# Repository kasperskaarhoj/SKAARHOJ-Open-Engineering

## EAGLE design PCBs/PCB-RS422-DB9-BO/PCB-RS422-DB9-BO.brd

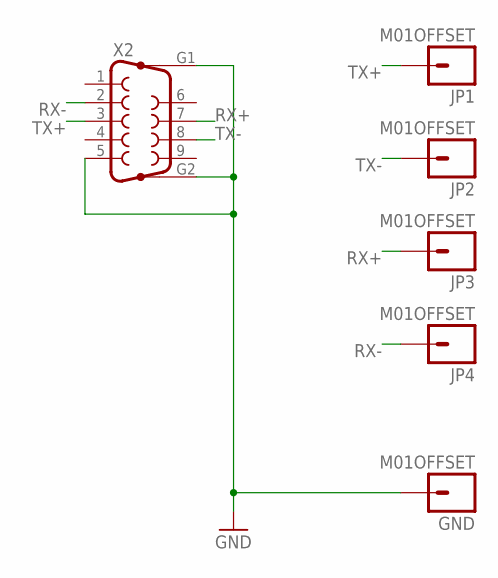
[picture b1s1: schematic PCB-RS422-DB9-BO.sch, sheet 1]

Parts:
GND: M01OFFSET; 1X01_OFFSET
JP1, JP2, JP3, JP4: M01OFFSET; 1X01_OFFSET
X2: F09HP

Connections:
GND: GND.1, X2.5, X2.G1, X2.G2
RX+: JP3.1, X2.7
RX-: JP4.1, X2.2
TX+: JP1.1, X2.3
TX-: JP2.1, X2.8

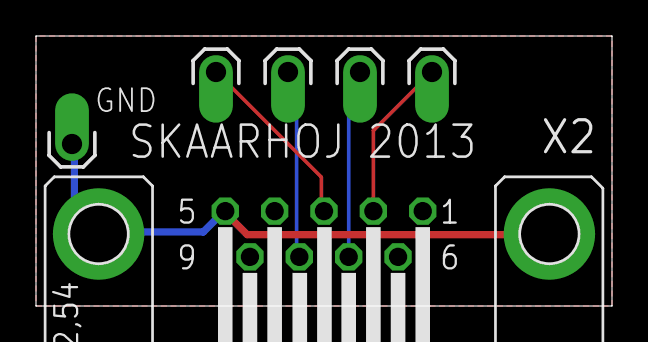
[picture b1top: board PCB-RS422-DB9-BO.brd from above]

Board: 2 copper layers, 32.0 x 15.0 mm, 6 parts (0 on the bottom side), 5 nets.

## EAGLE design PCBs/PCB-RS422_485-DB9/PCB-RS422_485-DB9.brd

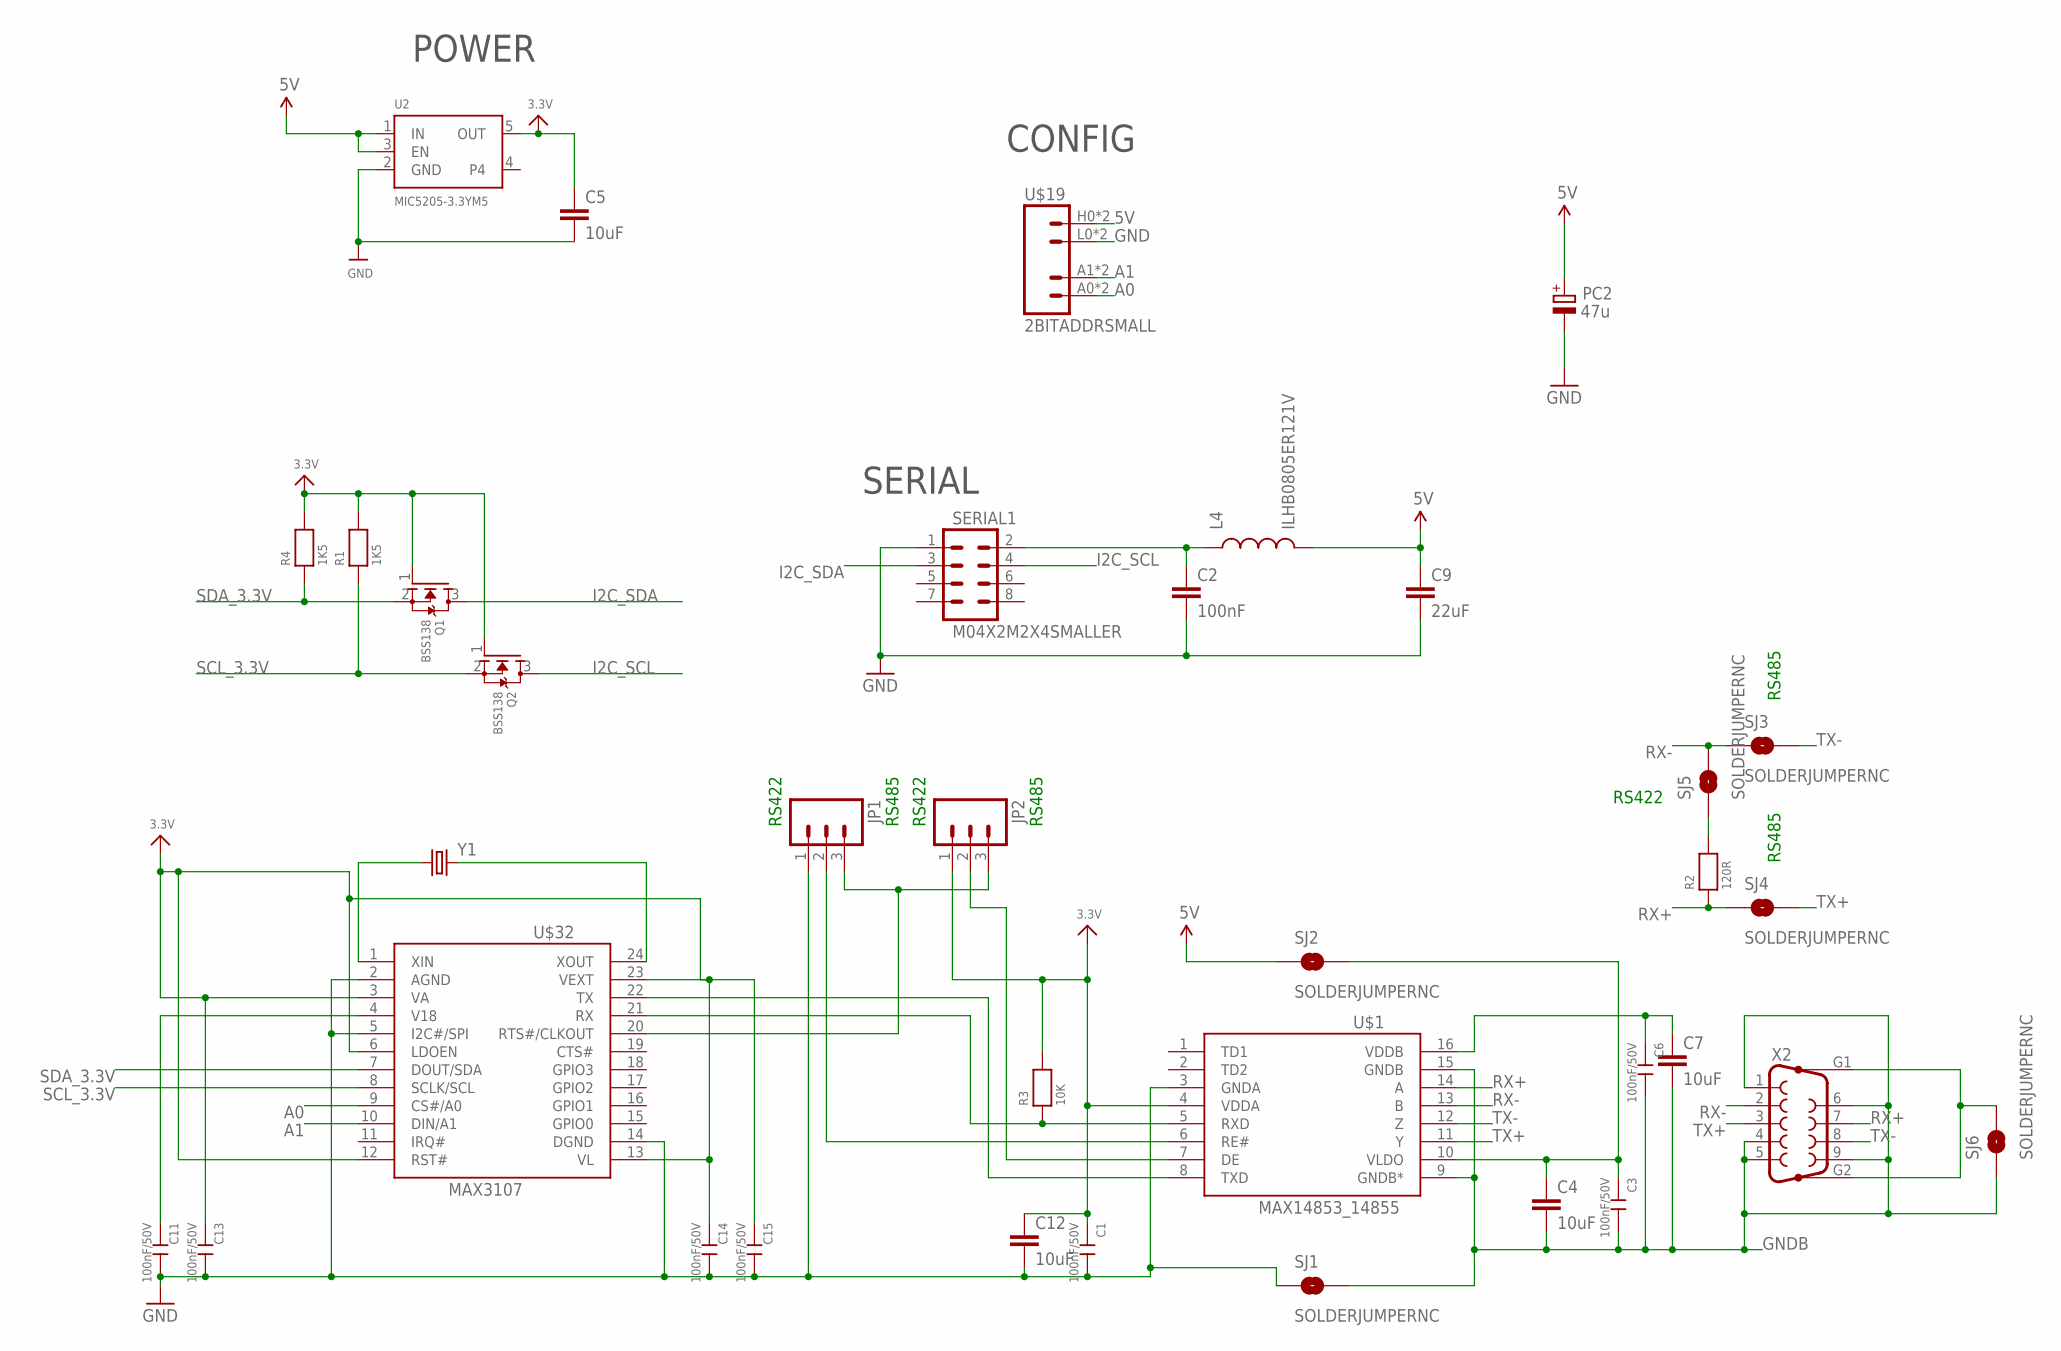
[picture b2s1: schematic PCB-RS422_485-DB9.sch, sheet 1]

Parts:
C1, C3, C6, C11, C13, C14, C15: 100nF/50V; C0603
C2: 100nF; 0603-CAP
C4, C5, C7, C12: 10uF; 0805
C9: 22uF; 0805
JP1, JP2: M03LOCK; 1X03_LOCK
L4: ILHB0805ER121V; 0805
PC2: 47u; PANASONIC_D
Q1, Q2: BSS138; SOT23-R
R1, R4: 1K5; 0603
R2: 120R; 0603
R3: 10K; 0603
SERIAL1: M04X2M2X4SMALLER; M2X4SMALLER
SJ1, SJ2, SJ3, SJ4, SJ5, SJ6: SOLDERJUMPERNC; SJ_2S
U2: MIC5205-3.3YM5; SOT23-5
U$1: MAX14853_14855; SO-16W
U$19: 2BITADDRSMALL; 2BITADDR_SMALL
U$32: MAX3107; SSOP24
X2: F09HP
Y1: CRYSTALHC49US; HC49US

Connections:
3.3V: C1.1, C5.1, C12.1, C13.1, C14.1, C15.1, JP2.1, Q1.1 (G), Q2.1 (G), R1.2, R3.2, R4.2, U2.5 (OUT), U$1.4 (VDDA), U$32.3 (VA), U$32.6 (LDOEN), U$32.12 (RST#), U$32.13 (VL), U$32.23 (VEXT)
5V: C9.1, L4.2, PC2.+, SJ2.1, U2.1 (IN), U2.3 (EN), U$19.H0 (VCC), U$19.H1 (VCC)
A0: U$19.A0 (A1), U$19.AS0 (A1), U$32.9 (CS#/A0)
A1: U$19.A1 (A2), U$19.AS1 (A2), U$32.10 (DIN/A1)
GND: C1.2, C2.2, C5.2, C9.2, C11.2, C12.2, C13.2, C14.2, C15.2, JP1.1, PC2.-, SERIAL1.1, SJ1.1, U2.2 (GND), U$1.3 (GNDA), U$19.L0 (GND), U$19.L1 (GND), U$32.2 (AGND), U$32.5 (I2C#/SPI), U$32.14 (DGND)
GNDB: C3.2, C4.2, C6.2, C7.2, SJ1.2, SJ6.1, U$1.9 (GNDB*), U$1.15 (GNDB), X2.1, X2.4, X2.5, X2.6, X2.9
I2C_SCL: Q2.3 (D), SERIAL1.4
I2C_SDA: Q1.3 (D), SERIAL1.3
unnamed: U$1.8 (TXD), U$32.22 (TX)
unnamed: R3.1, U$1.5 (RXD), U$32.21 (RX)
unnamed: C2.1, L4.1, SERIAL1.2
unnamed: R2.2, SJ5.1
unnamed: C3.1, C4.1, SJ2.2, U$1.10 (VLDO)
unnamed: C11.1, U$32.4 (V18)
unnamed: JP2.2, U$1.7 (DE)
unnamed: JP1.2, U$1.6 (RE#)
unnamed: SJ6.2, X2.G1, X2.G2
unnamed: JP1.3, JP2.3, U$32.20 (RTS#/CLKOUT)
unnamed: U$32.1 (XIN), Y1.1
unnamed: C6.1, C7.1, U$1.16 (VDDB)
unnamed: U$32.24 (XOUT), Y1.2
RX+: R2.1, SJ4.1, U$1.14 (A), X2.7
RX-: SJ3.1, SJ5.2, U$1.13 (B), X2.2
SCL_3.3V: Q2.2 (S), R1.1, U$32.8 (SCLK/SCL)
SDA_3.3V: Q1.2 (S), R4.1, U$32.7 (DOUT/SDA)
TX+: SJ4.2, U$1.11 (Y), X2.3
TX-: SJ3.2, U$1.12 (Z), X2.8

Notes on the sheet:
SERIAL
RS422
RS485
POWER
CONFIG

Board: 2 copper layers, 36 parts (0 on the bottom side), 27 nets, no tracks yet.

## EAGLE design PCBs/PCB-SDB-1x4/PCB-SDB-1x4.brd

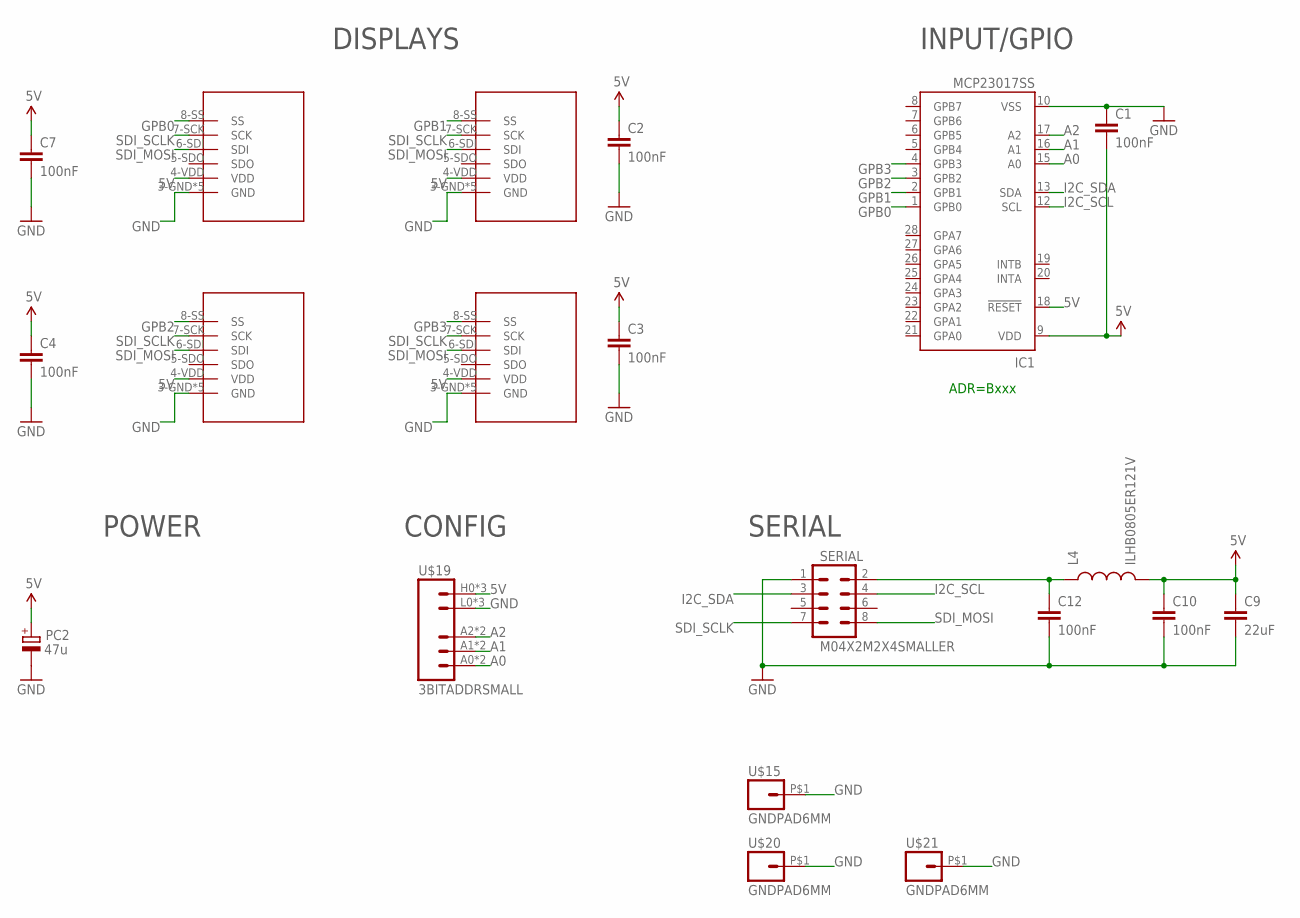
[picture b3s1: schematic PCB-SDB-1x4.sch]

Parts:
C1, C2, C3, C4, C7, C10, C12: 100nF; 0603-CAP
C9: 22uF; 0805
IC1: MCP23017SS; SSOP28; MPN MCP23017-E/SS
L4: ILHB0805ER121V; 0805
PC2: 47u; PANASONIC_D
SERIAL: M04X2M2X4SMALLER; M2X4SMALLER
SSW1, SSW2, SSW3, SSW4: SMART_DISPLAY
U$15, U$20, U$21: GNDPAD6MM; 3.2MMPAD6MM
U$19: 3BITADDRSMALL; 3BITADDR_SMALL

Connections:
5V: C1.2, C2.1, C3.1, C4.1, C7.1, C9.1, C10.1, IC1.9 (VDD), IC1.18 (!RESET), L4.2, PC2.+, SSW1.4-VDD (VDD), SSW2.4-VDD (VDD), SSW3.4-VDD (VDD), SSW4.4-VDD (VDD), U$19.H0 (VCC), U$19.H1 (VCC), U$19.H2 (VCC)
A0: IC1.15 (A0), U$19.A0, U$19.AS0 (A0)
A1: IC1.16 (A1), U$19.A1, U$19.AS1 (A1)
A2: IC1.17 (A2), U$19.A2, U$19.AS2 (A2)
ARD_5V: C12.1, L4.1, SERIAL.2
GND: C1.1, C2.2, C3.2, C4.2, C7.2, C9.2, C10.2, C12.2, IC1.10 (VSS), PC2.-, SERIAL.1, SSW1.3-GND (GND), SSW1.P$1 (GND), SSW1.P$2 (GND), SSW1.P$3 (GND), SSW1.P$4 (GND), SSW2.3-GND (GND), SSW2.P$1 (GND), SSW2.P$2 (GND), SSW2.P$3 (GND), SSW2.P$4 (GND), SSW3.3-GND (GND), SSW3.P$1 (GND), SSW3.P$2 (GND), SSW3.P$3 (GND), SSW3.P$4 (GND), SSW4.3-GND (GND), SSW4.P$1 (GND), SSW4.P$2 (GND), SSW4.P$3 (GND), SSW4.P$4 (GND), U$15.P$1, U$19.L0 (GND), U$19.L1 (GND), U$19.L2 (GND), U$20.P$1, U$21.P$1
GPB0: IC1.1 (GPB0), SSW1.8-SS (SS)
GPB1: IC1.2 (GPB1), SSW2.8-SS (SS)
GPB2: IC1.3 (GPB2), SSW3.8-SS (SS)
GPB3: IC1.4 (GPB3), SSW4.8-SS (SS)
I2C_SCL: IC1.12 (SCL), SERIAL.4
I2C_SDA: IC1.13 (SDA), SERIAL.3
SDI_MOSI: SERIAL.8, SSW1.6-SDI (SDI), SSW2.6-SDI (SDI), SSW3.6-SDI (SDI), SSW4.6-SDI (SDI)
SDI_SCLK: SERIAL.7, SSW1.7-SCK (SCK), SSW2.7-SCK (SCK), SSW3.7-SCK (SCK), SSW4.7-SCK (SCK)

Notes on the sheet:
ADR=Bxxx
INPUT/GPIO
POWER
SERIAL
DISPLAYS
CONFIG

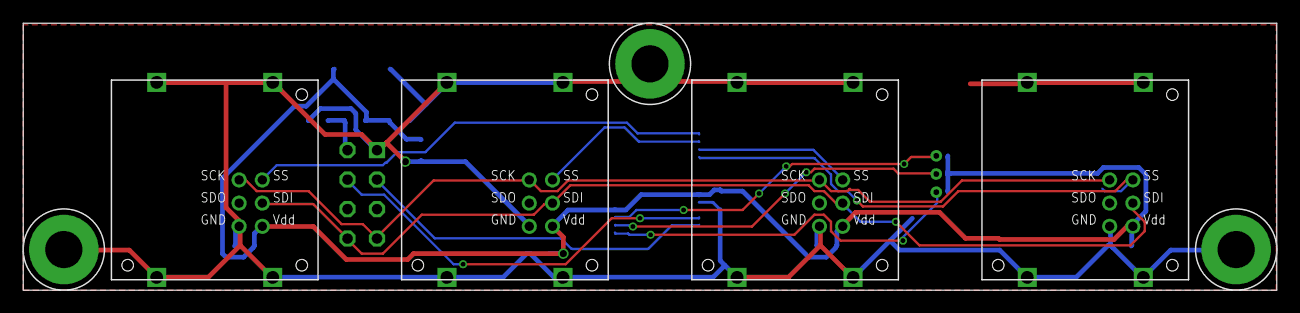
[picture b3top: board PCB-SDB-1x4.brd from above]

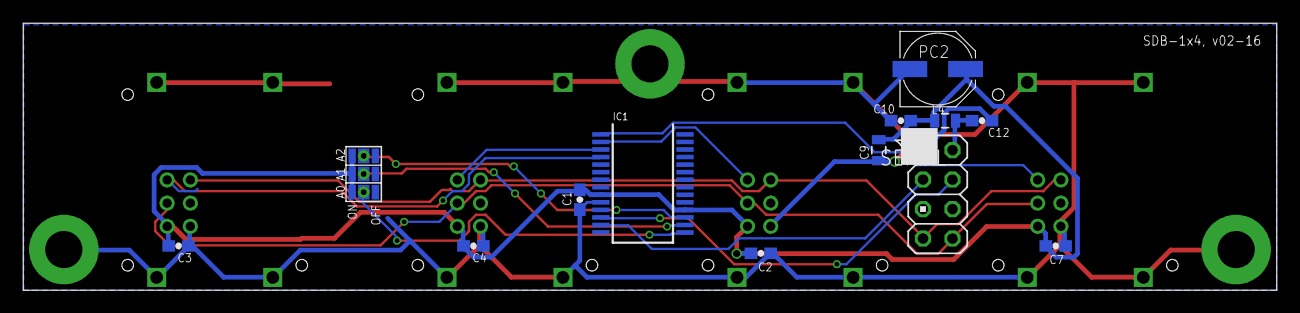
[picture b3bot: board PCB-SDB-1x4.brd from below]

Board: 2 copper layers, 108.0 x 23.0 mm, 20 parts (13 on the bottom side), 14 nets.

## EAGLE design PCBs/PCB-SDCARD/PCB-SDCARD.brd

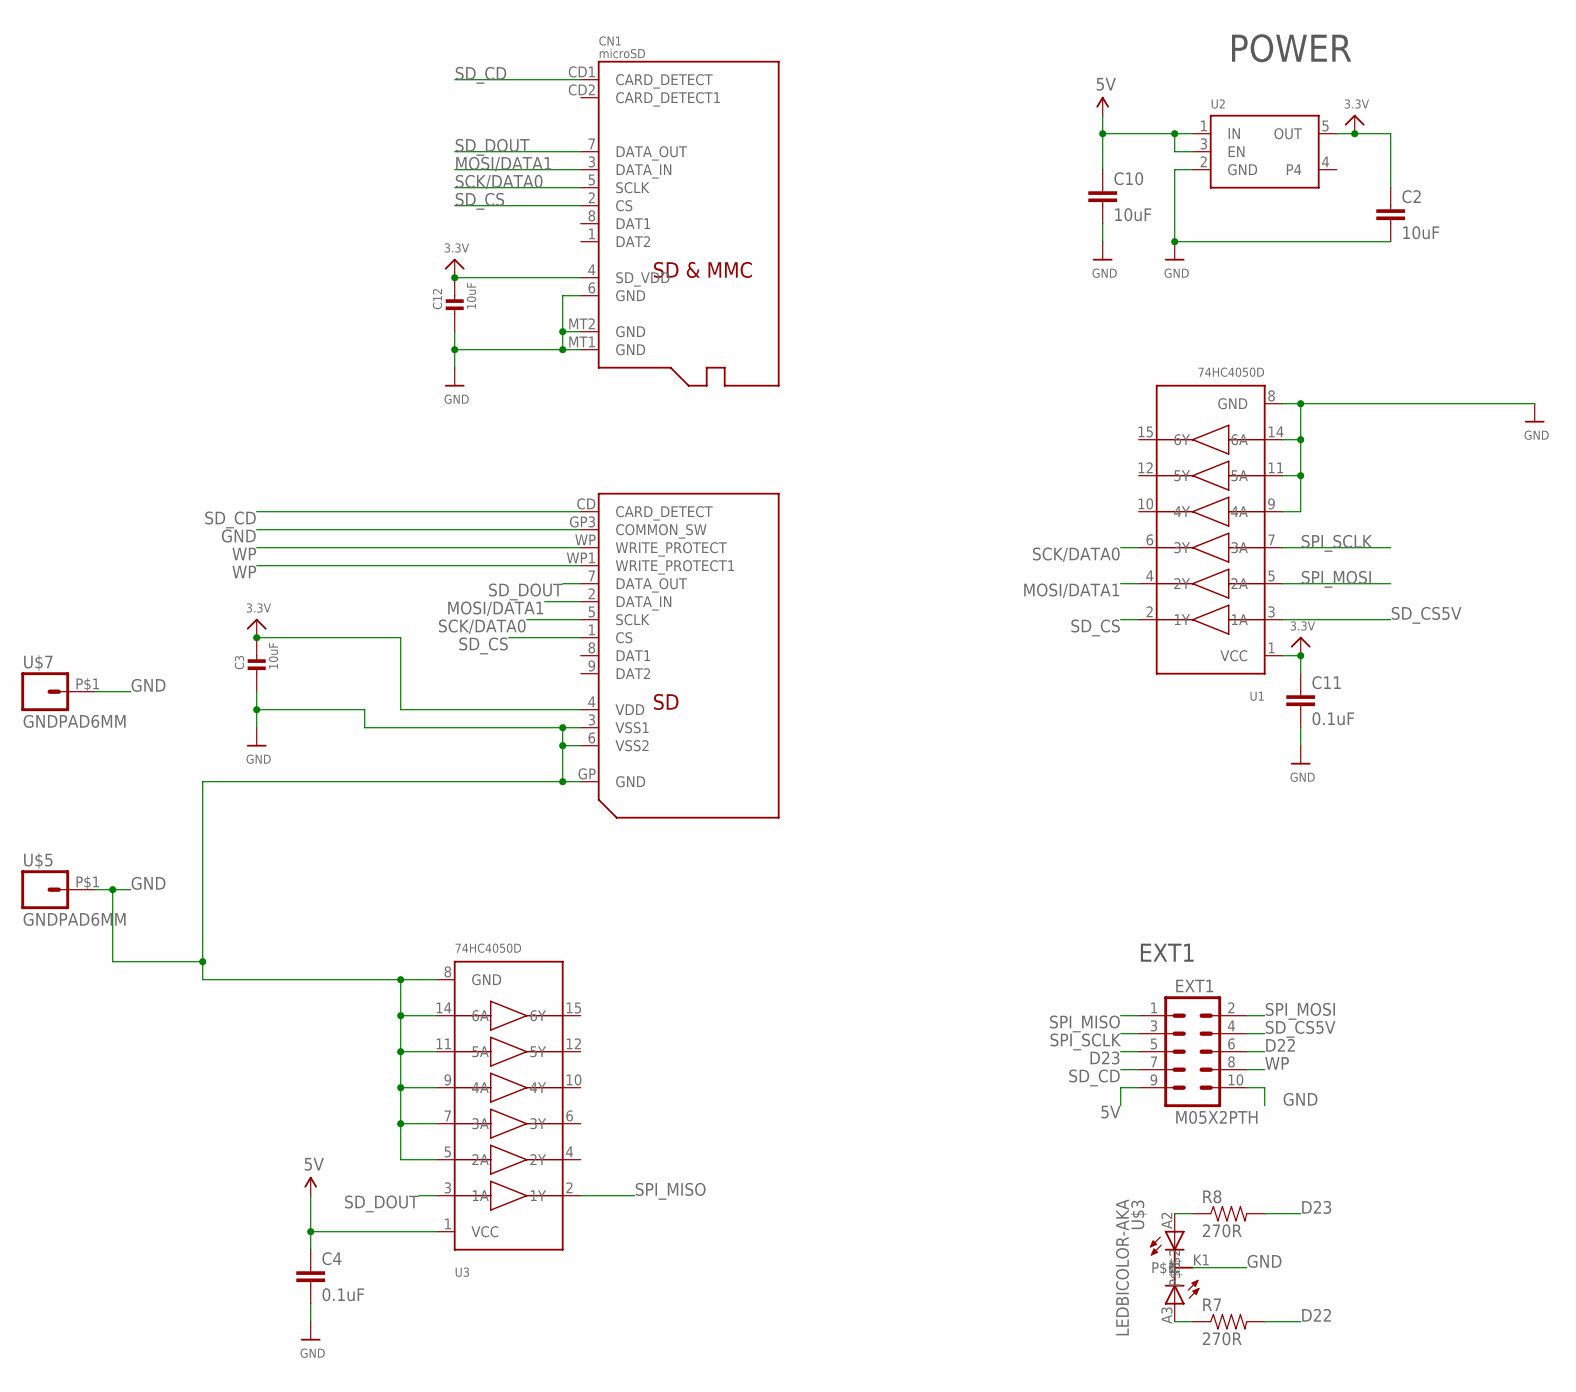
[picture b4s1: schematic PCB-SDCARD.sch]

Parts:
C2, C3, C10, C12: 10uF; 0805
C4, C11: 0.1uF; 0603-CAP
CN1: microSD; MICROSD
EXT1: M05X2PTH; AVR_ICSP
R7, R8: 270R; 0603-RES
U1, U3: 74HC4050D; TSSOP16
U2: VREG_SOT23-5; SOT23-5
U$2: SD06132; SD_LARGE
U$3: LEDBICOLOR-AKA; LED5MM-BICOLOR
U$5, U$7: GNDPAD6MM; 3.2MMPAD6MM

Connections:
3.3V: C2.1, C3.1, C11.1, C12.1, CN1.4 (SD_VDD), U1.1 (VCC), U2.5 (OUT), U$2.4 (VDD)
5V: C4.1, C10.1, EXT1.9, U2.1 (IN), U2.3 (EN), U3.1 (VCC)
D22: EXT1.6, R7.2
D23: EXT1.5, R8.2
GND: C2.2, C3.2, C4.2, C10.2, C11.2, C12.2, CN1.6 (GND), CN1.MT1 (GND), CN1.MT2 (GND), EXT1.10, U1.8 (GND), U1.9 (4A), U1.11 (5A), U1.14 (6A), U2.2 (GND), U3.5 (2A), U3.7 (3A), U3.8 (GND), U3.9 (4A), U3.11 (5A), U3.14 (6A), U$2.3 (VSS1), U$2.6 (VSS2), U$2.GP (GND), U$2.GP3 (COMMON_SW), U$3.K1, U$5.P$1, U$7.P$1
MOSI/DATA1: CN1.3 (DATA_IN), U1.4 (2Y), U$2.2 (DATA_IN)
unnamed: R8.1, U$3.A2
unnamed: R7.1, U$3.A3
SCK/DATA0: CN1.5 (SCLK), U1.6 (3Y), U$2.5 (SCLK)
SD_CD: CN1.CD1 (CARD_DETECT), EXT1.7, U$2.CD (CARD_DETECT)
SD_CS: CN1.2 (CS), U1.2 (1Y), U$2.1 (CS)
SD_CS5V: EXT1.4, U1.3 (1A)
SD_DOUT: CN1.7 (DATA_OUT), U3.3 (1A), U$2.7 (DATA_OUT)
SPI_MISO: EXT1.1, U3.2 (1Y)
SPI_MOSI: EXT1.2, U1.5 (2A)
SPI_SCLK: EXT1.3, U1.7 (3A)
WP: EXT1.8, U$2.WP (WRITE_PROTECT), U$2.WP1 (WRITE_PROTECT1)

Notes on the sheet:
POWER
EXT1

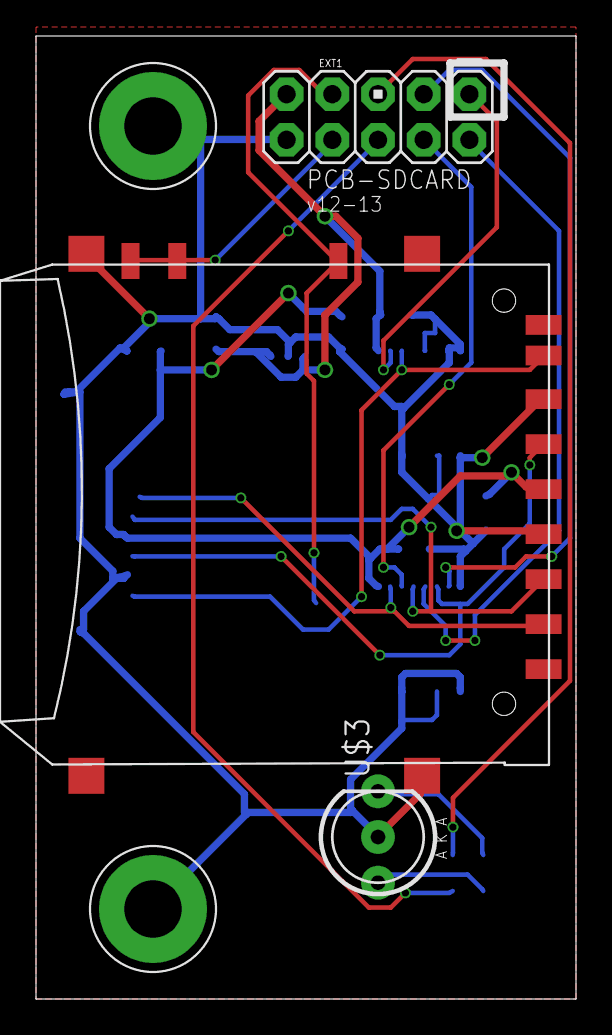
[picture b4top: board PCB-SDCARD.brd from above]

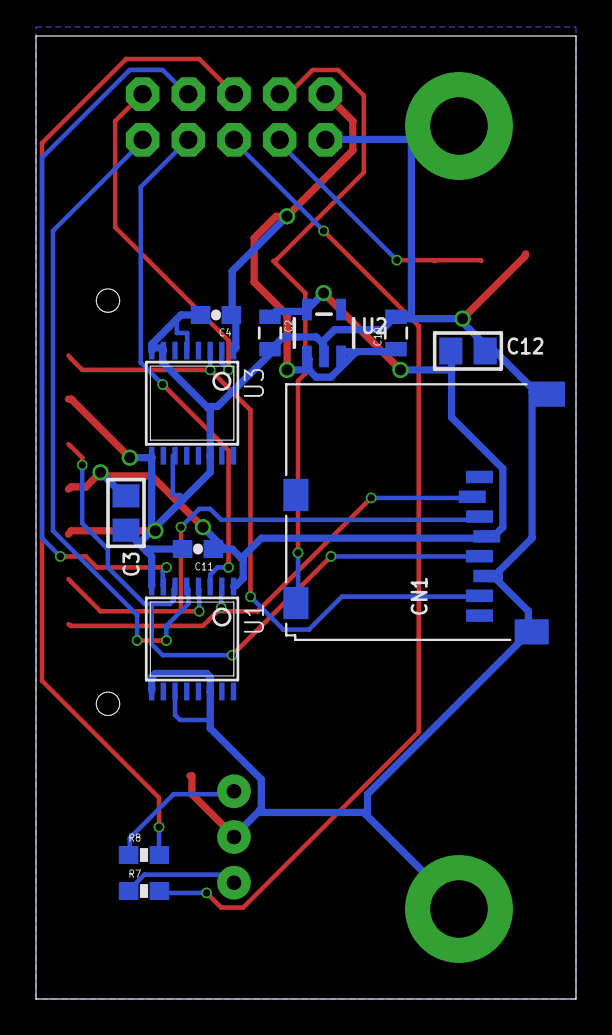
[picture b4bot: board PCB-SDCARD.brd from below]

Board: 4 copper layers, 30.0 x 53.5 mm, 17 parts (12 on the bottom side), 17 nets.

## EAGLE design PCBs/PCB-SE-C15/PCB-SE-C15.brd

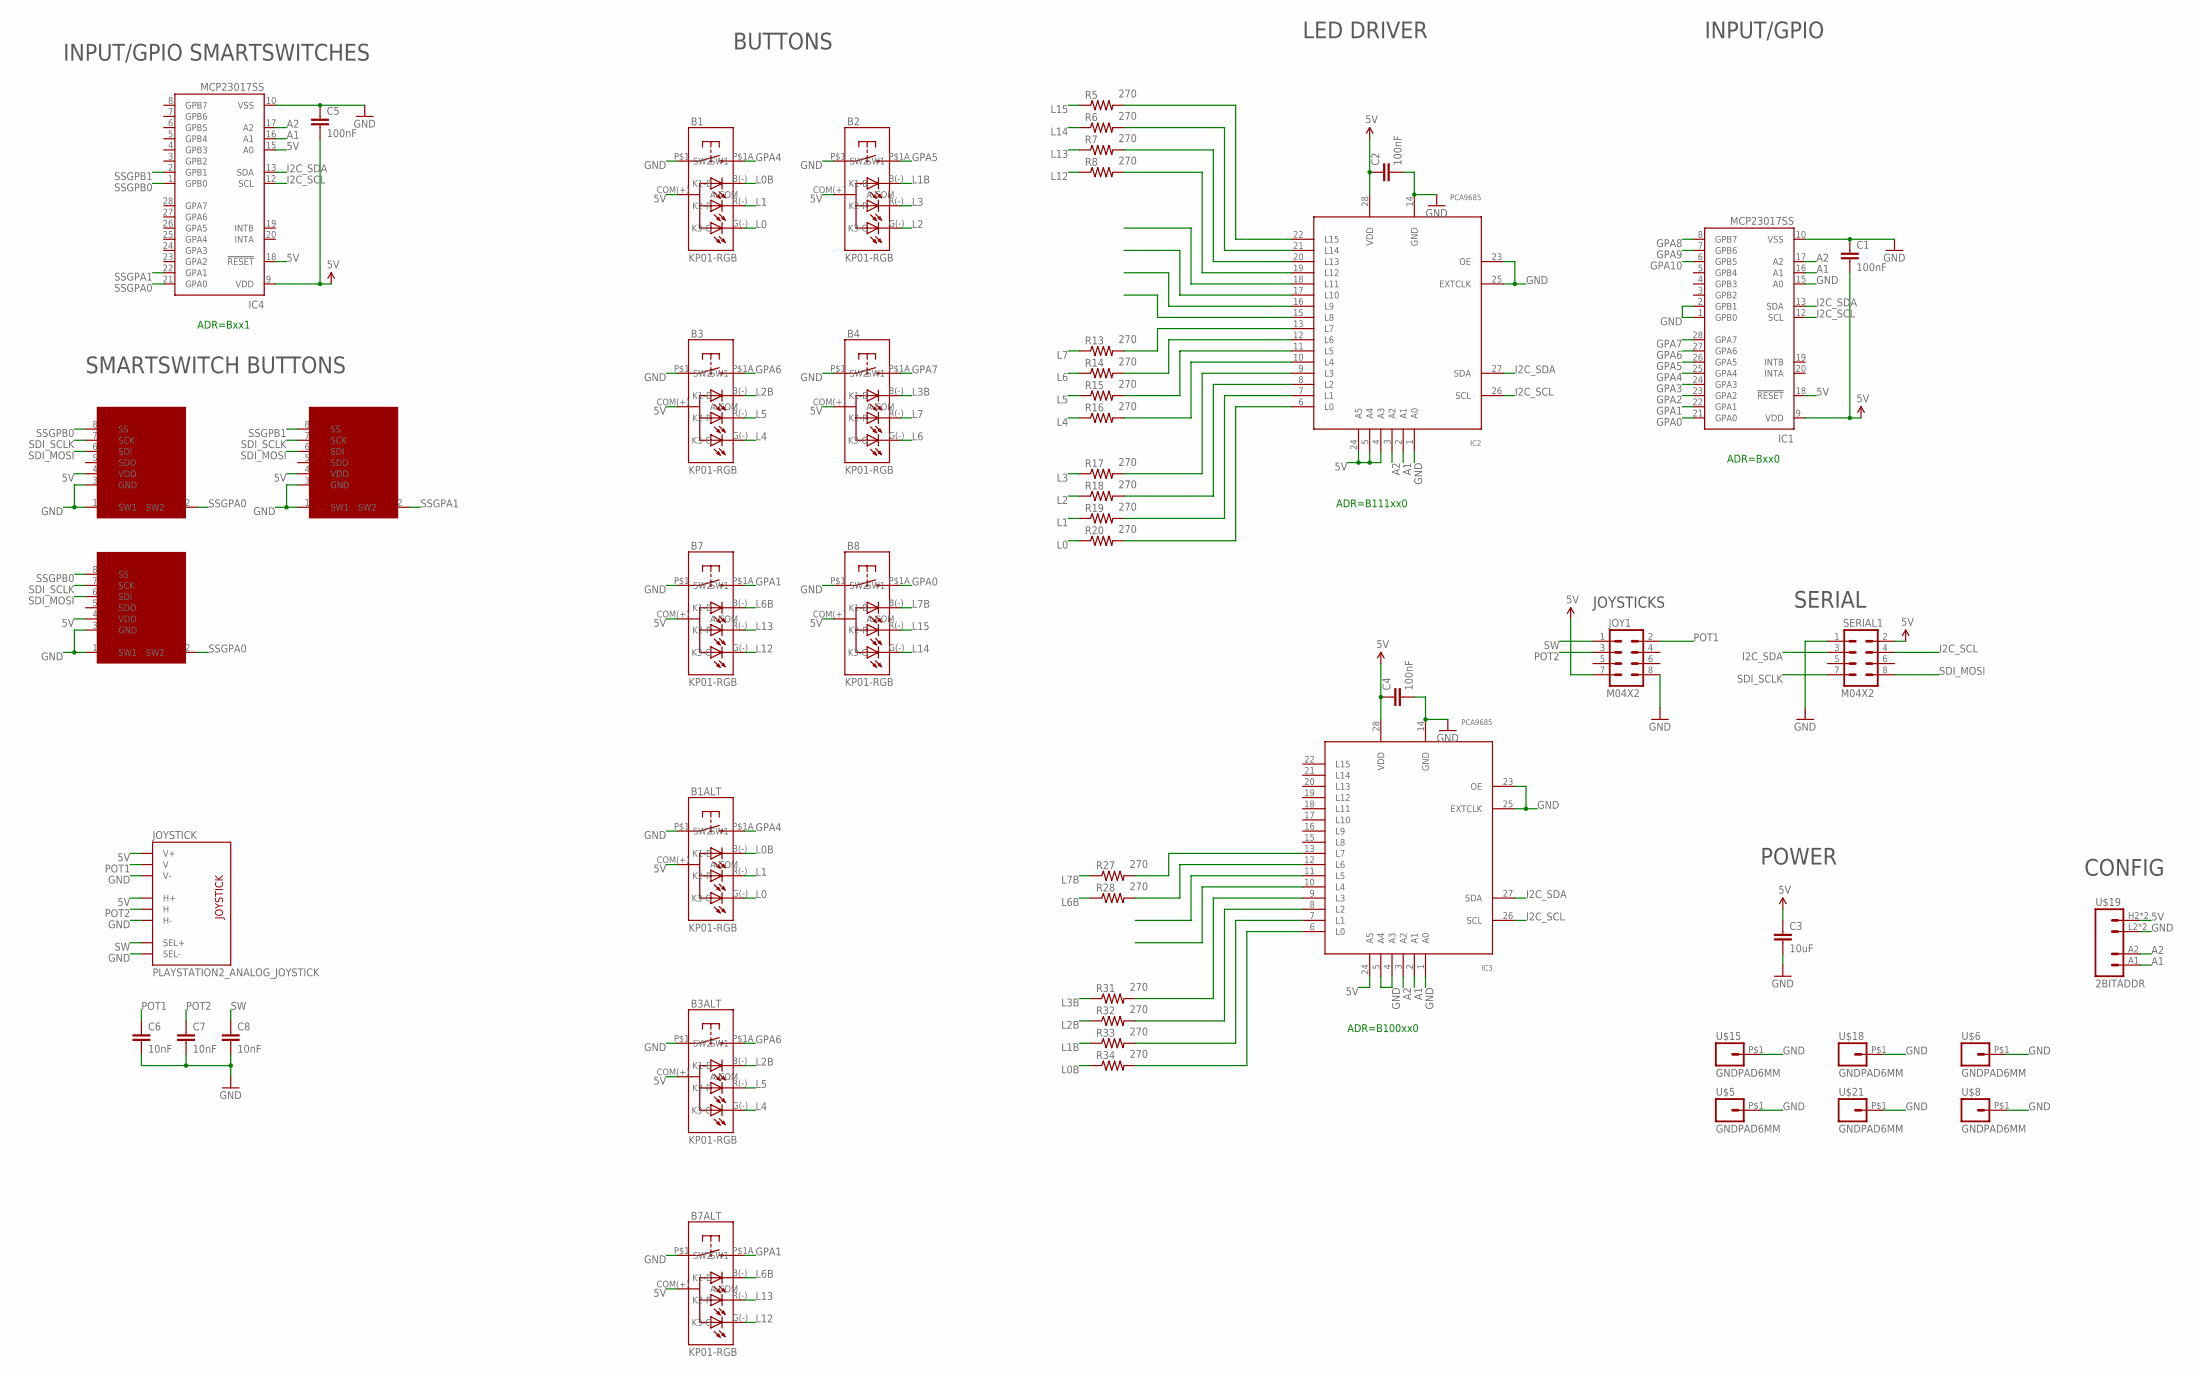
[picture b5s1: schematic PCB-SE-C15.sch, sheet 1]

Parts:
B1, B1ALT, B2, B3, B3ALT, B4, B7, B7ALT, B8: KP01-RGB; NKK-KP01
C1, C2, C4, C5: 100nF; 0603-CAP
C3: 10uF; 0805
C6, C7, C8: 10nF; 0603-CAP
IC1, IC4: MCP23017SS; SSOP28; MPN MCP23017-E/SS
IC2, IC3: PCA9685; TSSOP28
JOY1: M04X2; 2X4
JOYSTICK: PLAYSTATION2_ANALOG_JOYSTICK
R5, R6, R7, R8, R13, R14, R15, R16, R17, R18, R19, R20, R27, R28, R31, R32, R33, R34: 270; 0603-RES
SERIAL1: M04X2; 2X4
SSW1, SSW1ALT, SSW2: SMART_SWITCHSMART_SWITCH_8PIN; SMART_SWITCH
U$5, U$6, U$8, U$15, U$18, U$21: GNDPAD6MM; 3.2MMPAD6MM
U$19: 2BITADDR

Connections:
5V: B1.COM(+) (A-COM), B1ALT.COM(+) (A-COM), B2.COM(+) (A-COM), B3.COM(+) (A-COM), B3ALT.COM(+) (A-COM), B4.COM(+) (A-COM), B7.COM(+) (A-COM), B7ALT.COM(+) (A-COM), B8.COM(+) (A-COM), C1.2, C2.1, C3.1, C4.1, C5.2, IC1.9 (VDD), IC1.18 (!RESET), IC2.4 (A3), IC2.5 (A4), IC2.24 (A5), IC2.28 (VDD), IC3.24 (A5), IC3.28 (VDD), IC4.9 (VDD), IC4.15 (A0), IC4.18 (!RESET), JOY1.7, JOYSTICK.H1 (H+), JOYSTICK.V1 (V+), SERIAL1.2, SSW1.4 (VDD), SSW1ALT.4 (VDD), SSW2.4 (VDD), U$19.H2 (VCC), U$19.H3 (VCC)
A1: IC1.16 (A1), IC2.2 (A1), IC3.2 (A1), IC4.16 (A1), U$19.A1
A2: IC1.17 (A2), IC2.3 (A2), IC3.3 (A2), IC4.17 (A2), U$19.A2
GND: B1.P$1 (SW1), B1ALT.P$1 (SW1), B2.P$1 (SW1), B3.P$1 (SW1), B3ALT.P$1 (SW1), B4.P$1 (SW1), B7.P$1 (SW1), B7ALT.P$1 (SW1), B8.P$1 (SW1), C1.1, C2.2, C3.2, C4.2, C5.1, C6.2, C7.2, C8.2, IC1.1 (GPB0), IC1.2 (GPB1), IC1.10 (VSS), IC1.15 (A0), IC2.1 (A0), IC2.14 (GND), IC2.23 (OE), IC2.25 (EXTCLK), IC3.1 (A0), IC3.4 (A3), IC3.5 (A4), IC3.14 (GND), IC3.23 (OE), IC3.25 (EXTCLK), IC4.10 (VSS), JOY1.8, JOYSTICK.B2A (SEL-), JOYSTICK.H3 (H-), JOYSTICK.V3 (V-), SERIAL1.1, SSW1.1 (SW1), SSW1.3 (GND), SSW1ALT.1 (SW1), SSW1ALT.3 (GND), SSW2.1 (SW1), SSW2.3 (GND), U$5.P$1, U$6.P$1, U$8.P$1, U$15.P$1, U$18.P$1, U$19.L2 (GND), U$19.L3 (GND), U$21.P$1
GPA0: B8.P$1A (SW2), IC1.21 (GPA0)
GPA1: B7.P$1A (SW2), B7ALT.P$1A (SW2), IC1.22 (GPA1)
GPA2: IC1.23 (GPA2)
GPA3: IC1.24 (GPA3)
GPA4: B1.P$1A (SW2), B1ALT.P$1A (SW2), IC1.25 (GPA4)
GPA5: B2.P$1A (SW2), IC1.26 (GPA5)
GPA6: B3.P$1A (SW2), B3ALT.P$1A (SW2), IC1.27 (GPA6)
GPA7: B4.P$1A (SW2), IC1.28 (GPA7)
GPA8: IC1.8 (GPB7)
GPA9: IC1.7 (GPB6)
GPA10: IC1.6 (GPB5)
I2C_SCL: IC1.12 (SCL), IC2.26 (SCL), IC3.26 (SCL), IC4.12 (SCL), SERIAL1.4
I2C_SDA: IC1.13 (SDA), IC2.27 (SDA), IC3.27 (SDA), IC4.13 (SDA), SERIAL1.3
L0: B1.G(-) (K3-G), B1ALT.G(-) (K3-G), R20.1
L0B: B1.B(-) (K1-B), B1ALT.B(-) (K1-B), R34.1
L1: B1.R(-) (K2-R), B1ALT.R(-) (K2-R), R19.1
L1B: B2.B(-) (K1-B), R33.1
L2: B2.G(-) (K3-G), R18.1
L2B: B3.B(-) (K1-B), B3ALT.B(-) (K1-B), R32.1
L3: B2.R(-) (K2-R), R17.1
L3B: B4.B(-) (K1-B), R31.1
L4: B3.G(-) (K3-G), B3ALT.G(-) (K3-G), R16.1
L5: B3.R(-) (K2-R), B3ALT.R(-) (K2-R), R15.1
L6: B4.G(-) (K3-G), R14.1
L6B: B7.B(-) (K1-B), B7ALT.B(-) (K1-B), R28.1
L7: B4.R(-) (K2-R), R13.1
L7B: B8.B(-) (K1-B), R27.1
L12: B7.G(-) (K3-G), B7ALT.G(-) (K3-G), R8.1
L13: B7.R(-) (K2-R), B7ALT.R(-) (K2-R), R7.1
L14: B8.G(-) (K3-G), R6.1
L15: B8.R(-) (K2-R), R5.1
unnamed: IC3.13 (L7), R27.2
unnamed: IC3.12 (L6), R28.2
unnamed: IC2.13 (L7), R13.2
unnamed: IC2.12 (L6), R14.2
unnamed: IC2.11 (L5), R15.2
unnamed: IC2.10 (L4), R16.2
unnamed: IC2.9 (L3), R17.2
unnamed: IC2.8 (L2), R18.2
unnamed: IC2.7 (L1), R19.2
unnamed: IC3.9 (L3), R31.2
unnamed: IC3.8 (L2), R32.2
unnamed: IC3.7 (L1), R33.2
unnamed: IC3.6 (L0), R34.2
unnamed: IC2.6 (L0), R20.2
unnamed: IC2.19 (L12), R8.2
unnamed: IC2.20 (L13), R7.2
unnamed: IC2.21 (L14), R6.2
unnamed: IC2.22 (L15), R5.2
POT1: C6.1, JOY1.2, JOYSTICK.V2 (V)
POT2: C7.1, JOY1.3, JOYSTICK.H2 (H)
SDI_MOSI: SERIAL1.8, SSW1.6 (SDI), SSW1ALT.6 (SDI), SSW2.6 (SDI)
SDI_SCLK: SERIAL1.7, SSW1.7 (SCK), SSW1ALT.7 (SCK), SSW2.7 (SCK)
SSGPA0: IC4.21 (GPA0), SSW1.2 (SW2), SSW1ALT.2 (SW2)
SSGPA1: IC4.22 (GPA1), SSW2.2 (SW2)
SSGPB0: IC4.1 (GPB0), SSW1.8 (SS), SSW1ALT.8 (SS)
SSGPB1: IC4.2 (GPB1), SSW2.8 (SS)
SW: C8.1, JOY1.1, JOYSTICK.B1A (SEL+)

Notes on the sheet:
ADR=B111xx0
ADR=Bxx0
BUTTONS
LED DRIVER
INPUT/GPIO
POWER
ADR=B100xx0
ADR=Bxx1
INPUT/GPIO SMARTSWITCHES
SERIAL
SMARTSWITCH BUTTONS
JOYSTICKS
CONFIG

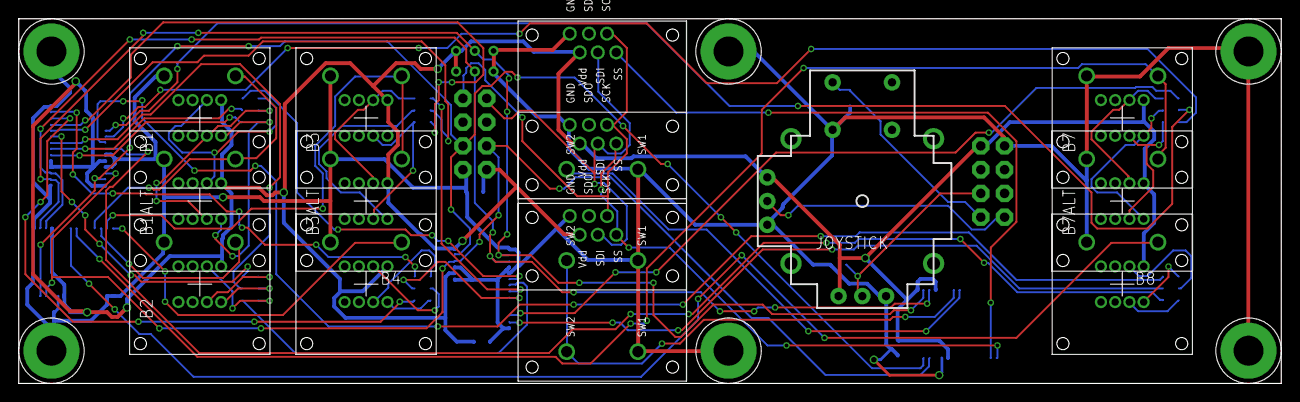
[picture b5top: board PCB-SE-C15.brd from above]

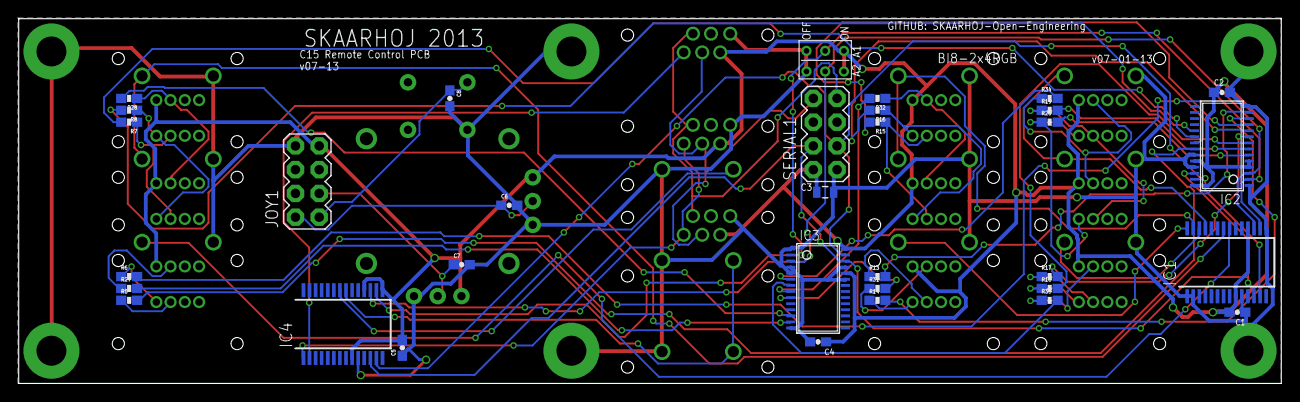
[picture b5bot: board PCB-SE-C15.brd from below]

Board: 2 copper layers, 135.0 x 39.0 mm, 52 parts (33 on the bottom side), 57 nets.

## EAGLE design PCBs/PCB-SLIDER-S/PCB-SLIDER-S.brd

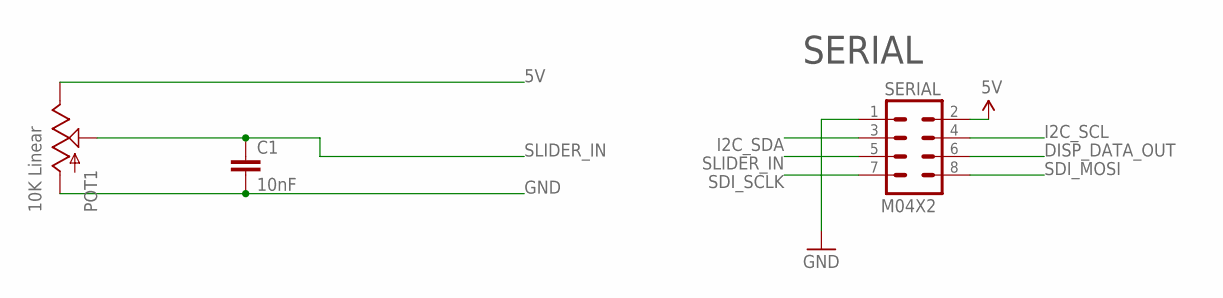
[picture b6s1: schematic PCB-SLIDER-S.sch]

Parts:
C1: 10nF; 0603-CAP
POT1: 10K Linear; SLIDER60
SERIAL: M04X2; 2X4

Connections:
5V: POT1.1 (E), SERIAL.2
DISP_DATA_OUT: SERIAL.6
GND: C1.2, POT1.3 (A), SERIAL.1
I2C_SCL: SERIAL.4
I2C_SDA: SERIAL.3
SDI_MOSI: SERIAL.8
SDI_SCLK: SERIAL.7
SLIDER_IN: C1.1, POT1.2A (S), SERIAL.5

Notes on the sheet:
SERIAL

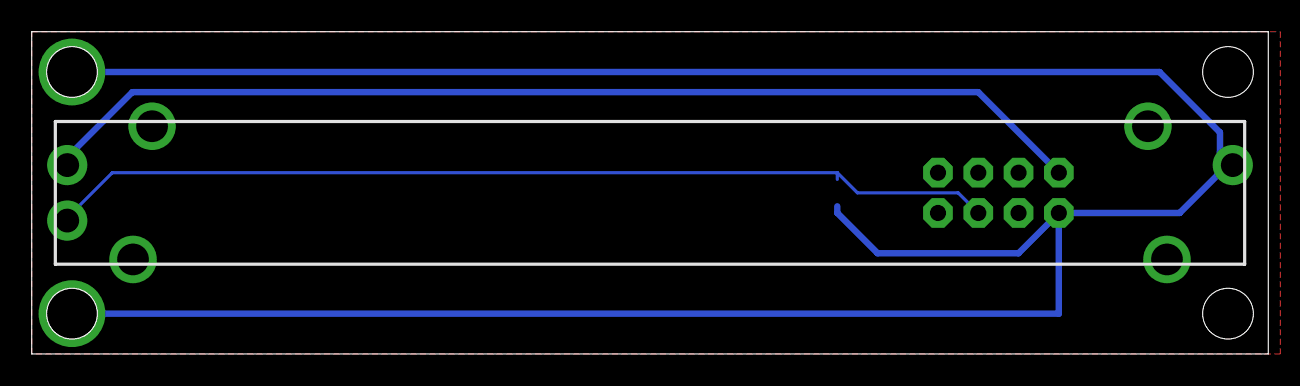
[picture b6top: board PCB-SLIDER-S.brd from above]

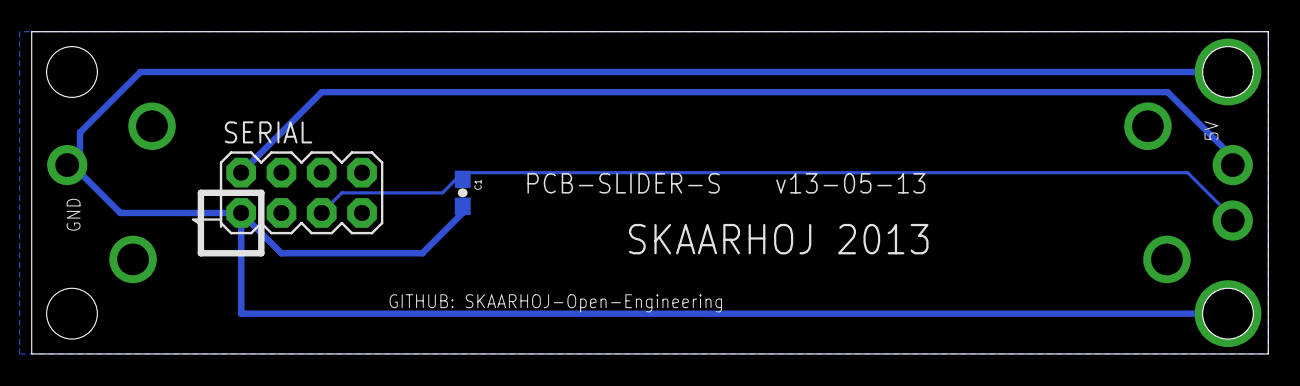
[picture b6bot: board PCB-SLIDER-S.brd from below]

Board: 2 copper layers, 78.0 x 20.3 mm, 3 parts (2 on the bottom side), 3 nets.

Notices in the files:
parts and their libraries:
SparkFun: Licensing: CC v3.0 Share-Alike You are welcome to use this library for commercial purposes.
